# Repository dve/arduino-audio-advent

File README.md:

# arduino-audio-advent
Arduino based audio advent calendar

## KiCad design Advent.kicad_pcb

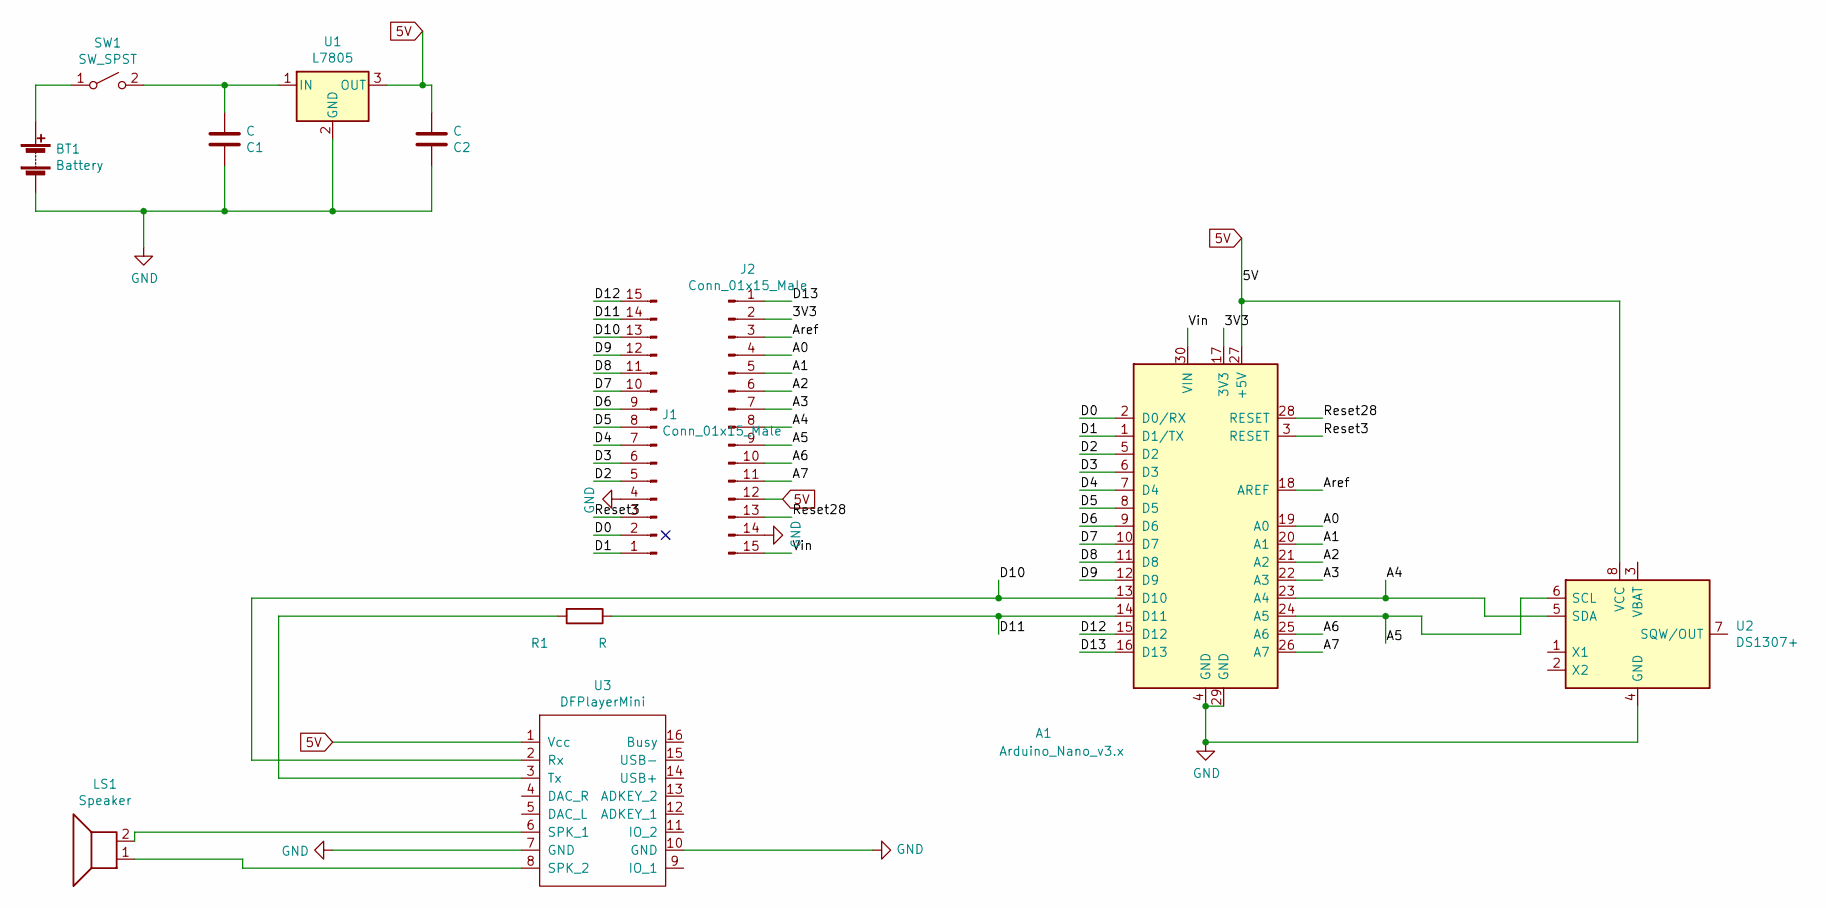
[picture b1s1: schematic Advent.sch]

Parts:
A1: Arduino_Nano_v3.x; Arduino_Nano
BT1: Battery; PinHeader_1x02_P2.54mm_Vertical
C1: C; C_Rect_L10.0mm_W4.0mm_P7.50mm_FKS3_FKP3
C2: C; C_Disc_D3.0mm_W2.0mm_P2.50mm
J1, J2: Conn_01x15_Male; PinHeader_1x15_P2.54mm_Vertical
LS1: Speaker; PinHeader_1x02_P2.54mm_Vertical
R1: R; R_Axial_DIN0411_L9.9mm_D3.6mm_P12.70mm_Horizontal
SW1: SW_SPST; PinHeader_1x02_P2.54mm_Vertical
U1: L7805; TO-220F-3_Vertical
U2: DS1307+; RTC-DS-1307
U3: DFPlayerMini

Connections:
5V: A1.27 (+5V), C2.2, J2.12, U1.3 (OUT), U2.8 (VCC), U3.1 (Vcc)
/3V3: A1.17 (3V3), J2.2
/A0: A1.19 (A0), J2.4
/A1: A1.20 (A1), J2.5
/A2: A1.21 (A2), J2.6
/A3: A1.22 (A3), J2.7
/A4: A1.23 (A4), J2.8, U2.5 (SDA)
/A5: A1.24 (A5), J2.9, U2.6 (SCL)
/A6: A1.25 (A6), J2.10
/A7: A1.26 (A7), J2.11
/Aref: A1.18 (AREF), J2.3
/D0: A1.2 (D0/RX), J1.2
/D1: A1.1 (D1/TX), J1.1
/D2: A1.5 (D2), J1.5
/D3: A1.6 (D3), J1.6
/D4: A1.7 (D4), J1.7
/D5: A1.8 (D5), J1.8
/D6: A1.9 (D6), J1.9
/D7: A1.10 (D7), J1.10
/D8: A1.11 (D8), J1.11
/D9: A1.12 (D9), J1.12
/D10: A1.13 (D10), J1.13, U3.2 (Rx)
/D11: A1.14 (D11), J1.14, R1.1
/D12: A1.15 (D12), J1.15
/D13: A1.16 (D13), J2.1
/Reset3: A1.3 (RESET), J1.3
/Reset28: A1.28 (RESET), J2.13
/Vin: A1.30 (VIN), J2.15
GND: A1.4 (GND), A1.29 (GND), BT1.2 (-), C1.1, C2.1, J1.4, J2.14, U1.2 (GND), U2.4 (GND), U3.7 (GND), U3.10 (GND)
unnamed: BT1.1 (+), SW1.1 (A)
unnamed: C1.2, SW1.2 (B), U1.1 (IN)
unnamed: LS1.1, U3.8 (SPK_2)
unnamed: LS1.2, U3.6 (SPK_1)
unnamed: R1.2, U3.3 (Tx)

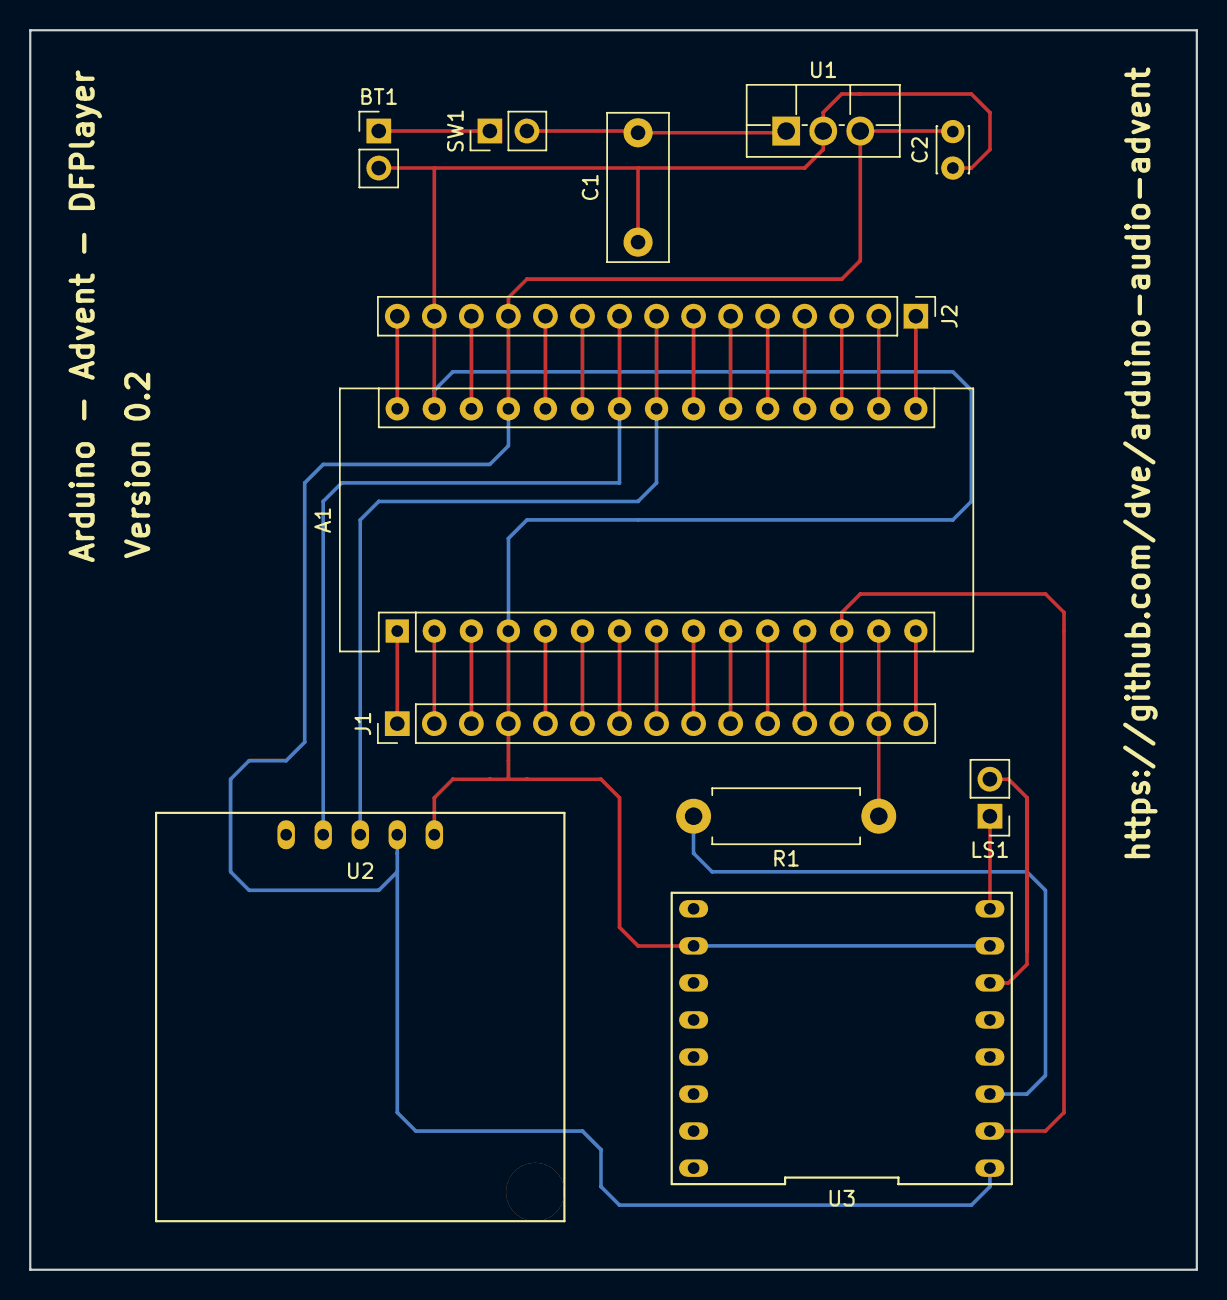
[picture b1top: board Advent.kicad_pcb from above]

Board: 2 copper layers, 80.0 x 85.0 mm, 12 parts (0 on the bottom side), 34 nets.
